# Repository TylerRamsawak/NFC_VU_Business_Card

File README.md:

# NFC VU Meter Business Card
I made a NFC business card themed to look like one of my TEAC A3340S VU meters. When you tap the card with your phone, the PEAK indicator lights up, just as it would on a real VU meter! I made this project because I have been calibrating, collecting, and repairing audio equipment for many many years now. Naturally, most of the machines have VU meters on them, and I feel as though they have become the staple representation of my hobby. Additionally, I needed a business card for career fair coming up in Spring.
<br>
<div class="table_component" role="region" tabindex="0">
<table>
    <caption>Updated BOM</caption>
    <thead>
        <tr>
            <th>Reference</th>
            <th>Quantity</th>
            <th>Value</th>
            <th>LCSC ID</th>
            <th>Price</th>
            <th>Ext. Price</th>
        </tr>
    </thead>
    <tbody>
        <tr>
            <td>U1</td>
            <td>1</td>
            <td>NT3H2111W0FHKH</td>
            <td>C710403</td>
            <td>1.09000</td>
            <td>$5.45</td>
        </tr>
        <tr>
            <td>R2</td>
            <td>1</td>
            <td>47 Ohm</td>
            <td>C23182</td>
            <td>0.00300</td>
            <td>$0.15</td>
        </tr>
        <tr>
            <td>D1</td>
            <td>1</td>
            <td>2V LED</td>
            <td>C2286</td>
            <td>0.03500</td>
            <td>$0.35</td>
        </tr>
        <tr>
            <td>C1</td>
            <td>1</td>
            <td>220nF</td>
            <td>C21120</td>
            <td>0.08100</td>
            <td>$0.81</td>
        </tr>
        <tr>
            <td>Total: $14.19 (after shipping+tax)</td>
        </tr>
    </tbody>
</table>
</div>
<h3>3D model</h3>

<h3>PCB</h3>

<h3>Schematic</h3>

<h3>BOM</h3>

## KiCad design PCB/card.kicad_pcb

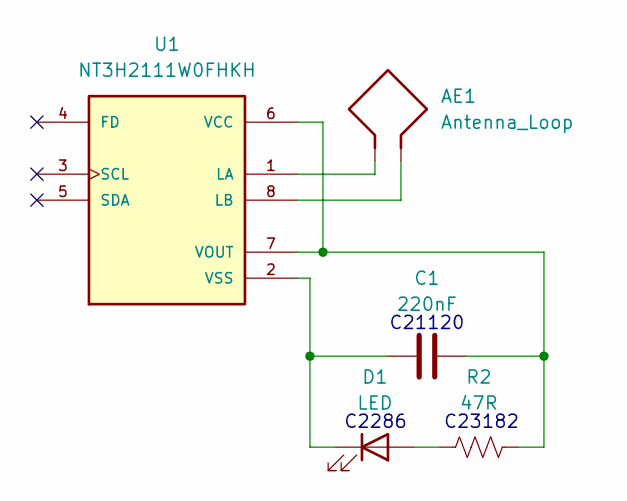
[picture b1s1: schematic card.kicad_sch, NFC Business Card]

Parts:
AE1: Antenna_Loop; 25X48MM_NFC
C1: 220nF; C_0603_1608Metric; LCSC C21120
D1: LED; LED_0603_1608Metric; LCSC C2286
R2: 47R; R_0603_1608Metric; LCSC C23182
U1: NT3H2111W0FHKH; QFN8P50_160X160X50L40X20N; LCSC C710403

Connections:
unnamed: D1.2 (A), R2.1
unnamed: C1.1, D1.1 (K), U1.2 (VSS)
unnamed: AE1.1, U1.1 (LA)
unnamed: AE1.2, U1.8 (LB)
unnamed: C1.2, R2.2, U1.6 (VCC), U1.7 (VOUT)

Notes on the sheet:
C2286
C23182
C21120

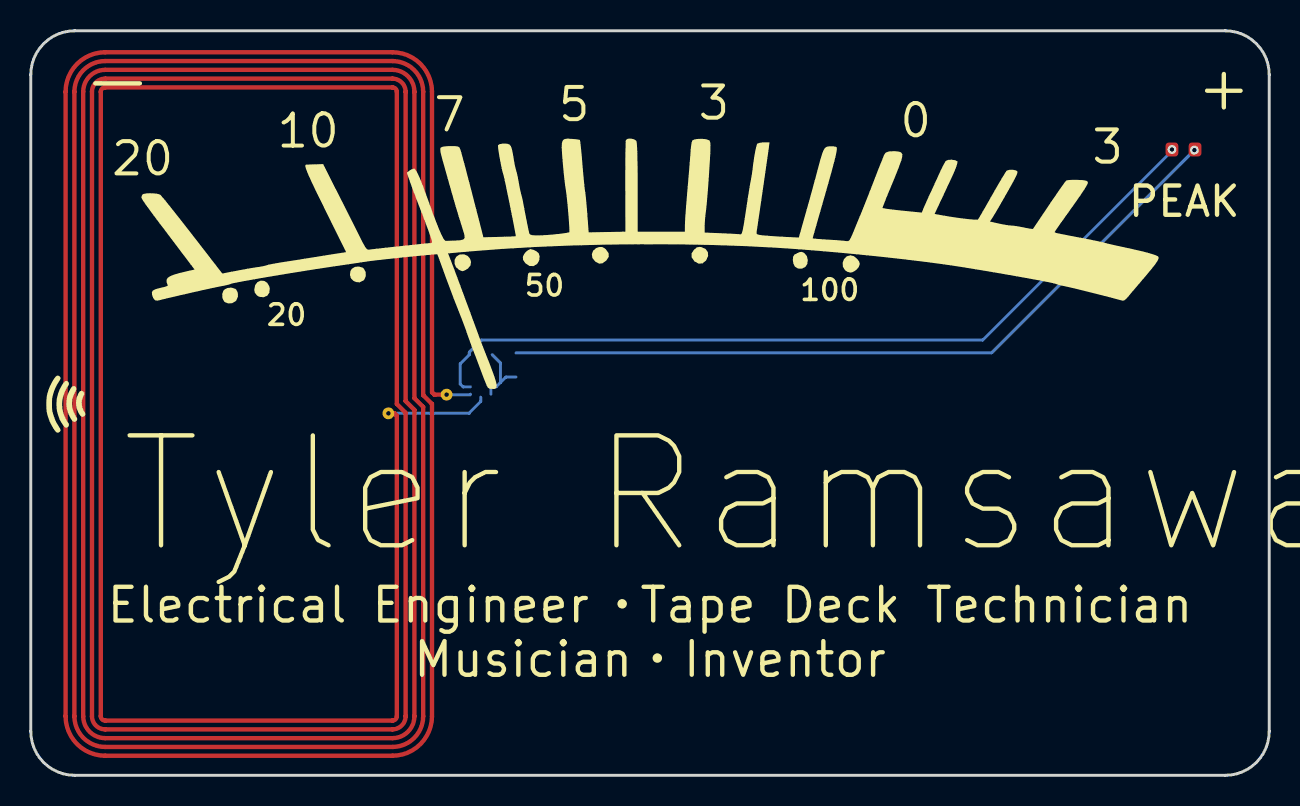
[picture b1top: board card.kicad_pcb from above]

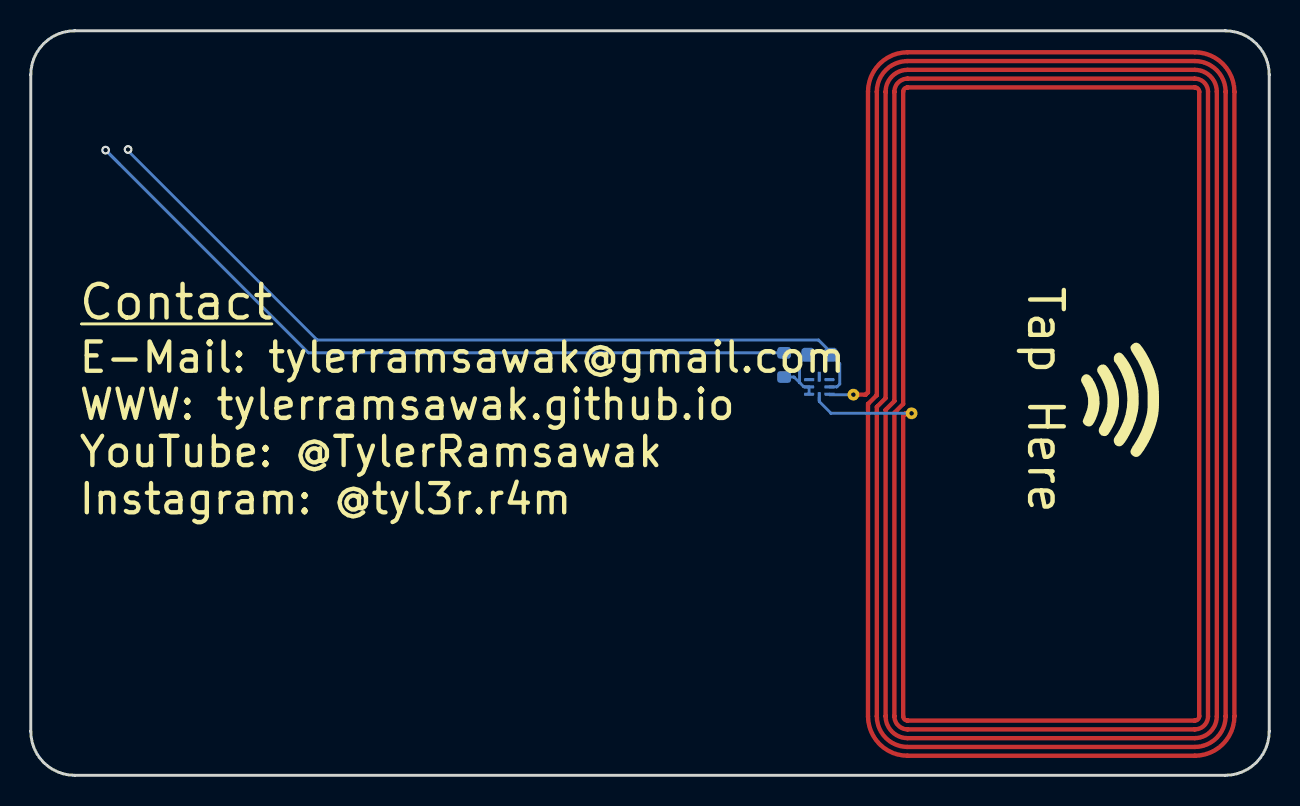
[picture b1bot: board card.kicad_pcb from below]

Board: 2 copper layers, 84.5 x 50.8 mm, 5 parts (3 on the bottom side), 5 nets.

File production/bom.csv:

Designator,Footprint,Quantity,Value,LCSC Part #
AE1,25X48MM_NFC,1,Antenna_Loop,
C1,0603,1,220nF,
D1,0603,1,LED,
R2,0603,1,47R,
U1,QFN8P50_160X160X50L40X20N,1,NT3H2111W0FHKH,

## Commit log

2025-11-11 Change image links to HTTPS in Journal.md
    Updated image links in Journal.md to use HTTPS for better accessibility and security.
2025-11-11 Initialize README with project description and images
    Added project details and images for NFC VU Meter business card.
2025-11-11 Update Journal.md with time and project details
    Added total time and date range for journal entries, along with details about the VU meter design process.
2025-11-14 Update README with BOM and project images
    Added updated Bill of Materials (BOM) and images for 3D model and PCB.
2025-11-14 Add price and total to components table in README
2025-11-14 Add price and extended price columns to BOM.csv
2025-11-14 Add missing fields to AE1 entry in BOM.csv
2025-11-14 Update Journal with shipment prep and PCB design details
    Added details for preparing shipment and design process for VU meter PCB, including images and measurements.
